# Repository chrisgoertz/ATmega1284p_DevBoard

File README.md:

# ATmega1284p_DevBoard
AVR Developement Board
## Features
### LCD Connector
Precofigured Header for standard Character Display pinouts.
### Buttons
8 on board push buttons. 4 with attached pull-up resistor, 4 with
attached pull-down resistor.
### FTDI Connector
Standard FTDI Connector with attachable DTR enable like Arduino. 
So it is possible to reset and programm the MCU via FTDI connection
if a bootloader is flashed and enabled.
### JTAG Connector
2 AVR JTAG Headers for programming and debugging.
### ISP
Standard 6-pin AVR ISP.
### Serial
6-pin connector with UART0 and UART1 and also VCC and GND.
### I²C
6-Pin Connector with SDA and SCL, VCC, GND and GPIO D7.
### LED-BARs
2 10-Channel LED-Bars, attached to PortA and PortC. 
Both channels can be separate enabled by jumper. Since all
LEDs are decoupled via MOSFETs, they don't affect the GPIOs.

## Pictures

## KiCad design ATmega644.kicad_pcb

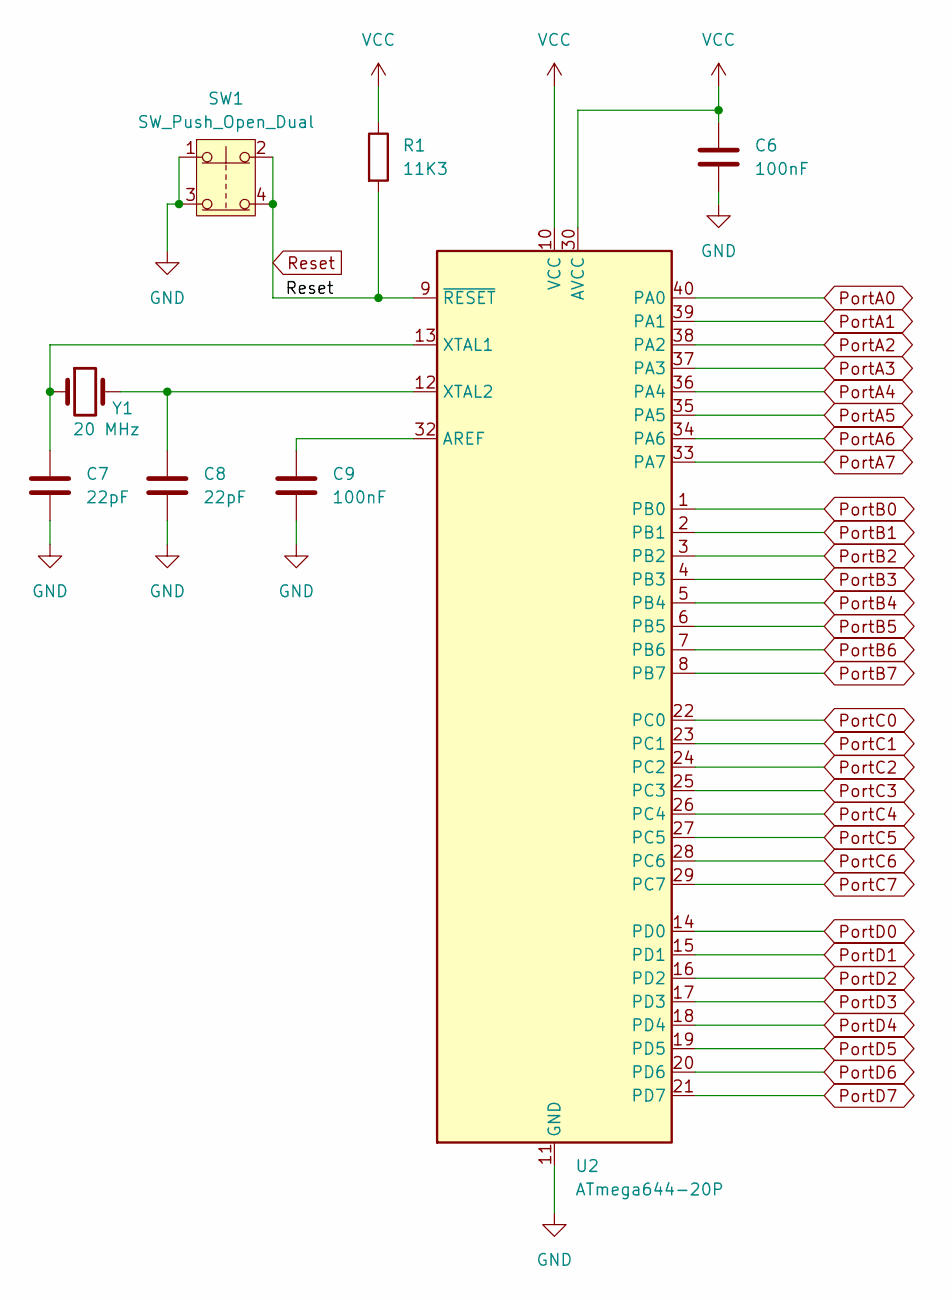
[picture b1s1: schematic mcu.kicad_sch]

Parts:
C6, C9: 100nF; C_0805_2012Metric_Pad1.18x1.45mm_HandSolder
C7, C8: 22pF; C_0805_2012Metric_Pad1.18x1.45mm_HandSolder
R1: 11K3; C_0805_2012Metric_Pad1.18x1.45mm_HandSolder
SW1: SW_Push_Open_Dual; SW_PUSH_6mm
U2: ATmega644-20P; DIP-40_W15.24mm
Y1: 20 MHz; Crystal_HC49-4H_Vertical

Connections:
GND: C6.2, C7.2, C8.2, C9.2, SW1.1, SW1.3, U2.11 (GND), U2.31 (GND); also elsewhere on the board
unnamed: C9.1, U2.32 (AREF)
unnamed: C7.1, U2.13 (XTAL1), Y1.1
unnamed: C8.1, U2.12 (XTAL2), Y1.2
PortA0: U2.40 (PA0); also elsewhere on the board
PortA1: U2.39 (PA1); also elsewhere on the board
PortA2: U2.38 (PA2); also elsewhere on the board
PortA3: U2.37 (PA3); also elsewhere on the board
PortA4: U2.36 (PA4); also elsewhere on the board
PortA5: U2.35 (PA5); also elsewhere on the board
PortA6: U2.34 (PA6); also elsewhere on the board
PortA7: U2.33 (PA7); also elsewhere on the board
PortB0: U2.1 (PB0); also elsewhere on the board
PortB1: U2.2 (PB1); also elsewhere on the board
PortB2: U2.3 (PB2); also elsewhere on the board
PortB3: U2.4 (PB3); also elsewhere on the board
PortB4: U2.5 (PB4); also elsewhere on the board
PortB5: U2.6 (PB5); also elsewhere on the board
PortB6: U2.7 (PB6); also elsewhere on the board
PortB7: U2.8 (PB7); also elsewhere on the board
PortC0: U2.22 (PC0); also elsewhere on the board
PortC1: U2.23 (PC1); also elsewhere on the board
PortC2: U2.24 (PC2); also elsewhere on the board
PortC3: U2.25 (PC3); also elsewhere on the board
PortC4: U2.26 (PC4); also elsewhere on the board
PortC5: U2.27 (PC5); also elsewhere on the board
PortC6: U2.28 (PC6); also elsewhere on the board
PortC7: U2.29 (PC7); also elsewhere on the board
PortD0: U2.14 (PD0); also elsewhere on the board
PortD1: U2.15 (PD1); also elsewhere on the board
PortD2: U2.16 (PD2); also elsewhere on the board
PortD3: U2.17 (PD3); also elsewhere on the board
PortD4: U2.18 (PD4); also elsewhere on the board
PortD5: U2.19 (PD5); also elsewhere on the board
PortD6: U2.20 (PD6); also elsewhere on the board
PortD7: U2.21 (PD7); also elsewhere on the board
Reset: R1.2, SW1.2, SW1.4, U2.9 (~RESET); also elsewhere on the board
VCC: C6.1, R1.1, U2.10 (VCC), U2.30 (AVCC); also elsewhere on the board

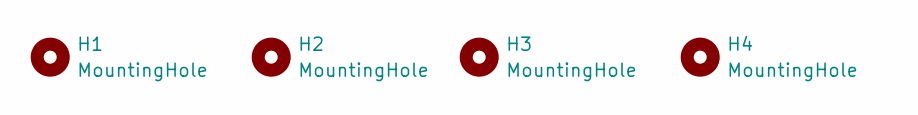
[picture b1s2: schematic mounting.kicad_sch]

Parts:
H1, H2, H3, H4: MountingHole; MountingHole_3.2mm_M3_DIN965

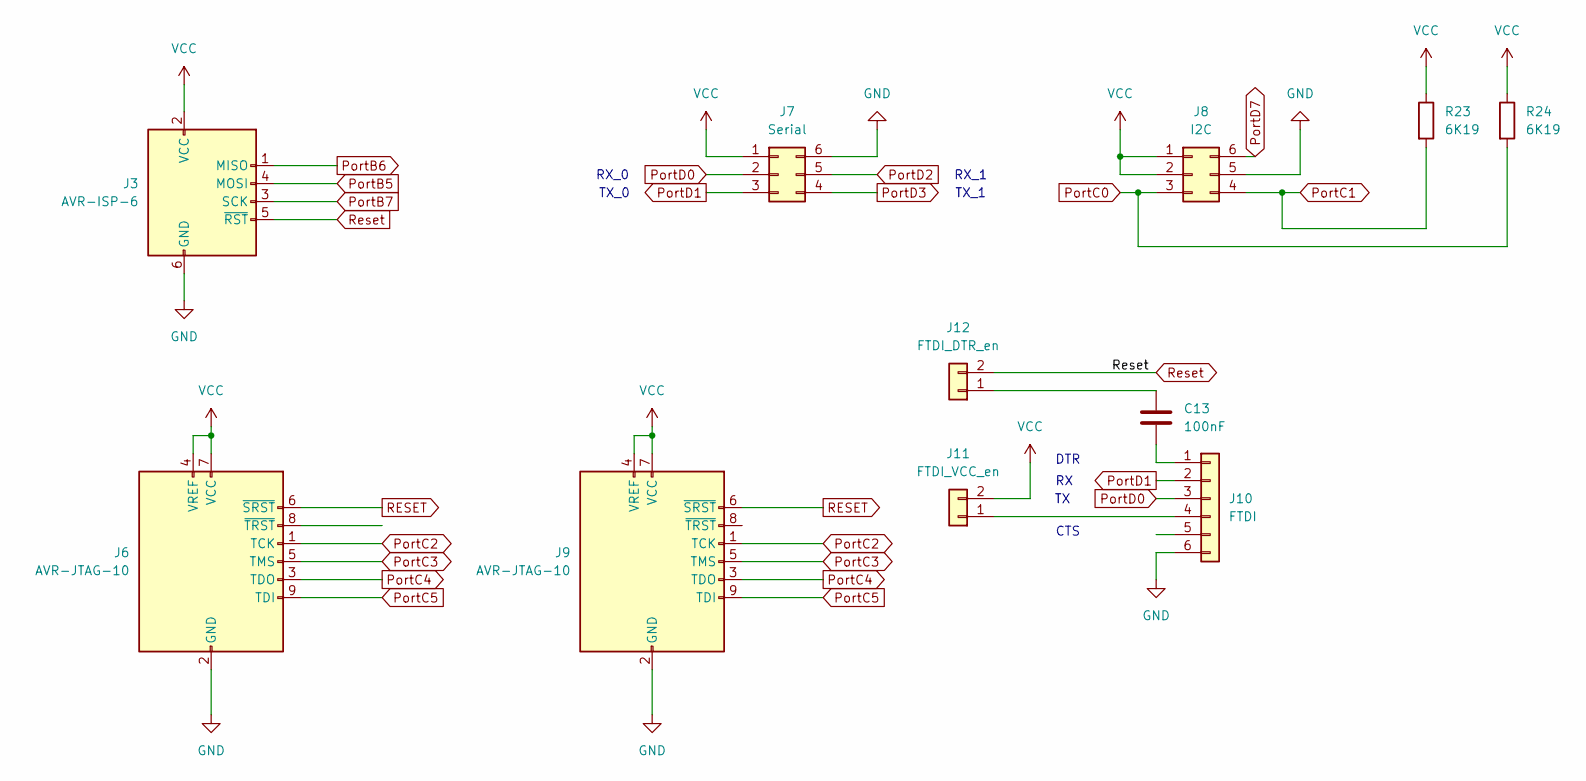
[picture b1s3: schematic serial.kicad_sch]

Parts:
C13: 100nF; LED_0805_2012Metric_Pad1.15x1.40mm_HandSolder
J3: AVR-ISP-6; IDC-Header_2x03_P2.54mm_Vertical
J6: AVR-JTAG-10; PinHeader_2x05_P2.54mm_Vertical
J7: Serial; IDC-Header_2x03_P2.54mm_Vertical
J8: I2C; IDC-Header_2x03_P2.54mm_Vertical
J9: AVR-JTAG-10; PinHeader_2x05_P1.27mm_Vertical_SMD
J10: FTDI; PinHeader_1x06_P2.54mm_Vertical
J11: FTDI_VCC_en; PinHeader_1x02_P2.54mm_Vertical
J12: FTDI_DTR_en; PinHeader_1x02_P2.54mm_Vertical
R23, R24: 6K19; L_1206_3216Metric_Pad1.42x1.75mm_HandSolder

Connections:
GND: J3.6 (GND), J6.2 (GND), J6.10 (GND), J7.6, J8.5, J9.2 (GND), J9.10 (GND), J10.6; also elsewhere on the board
unnamed: C13.2, J10.1
unnamed: J10.4, J11.1
unnamed: C13.1, J12.1
PortB5: J3.4 (MOSI); also elsewhere on the board
PortB6: J3.1 (MISO); also elsewhere on the board
PortB7: J3.3 (SCK); also elsewhere on the board
PortC0: J8.3, R24.2; also elsewhere on the board
PortC1: J8.4, R23.2; also elsewhere on the board
PortC2: J6.1 (TCK), J9.1 (TCK); also elsewhere on the board
PortC3: J6.5 (TMS), J9.5 (TMS); also elsewhere on the board
PortC4: J6.3 (TDO), J9.3 (TDO); also elsewhere on the board
PortC5: J6.9 (TDI), J9.9 (TDI); also elsewhere on the board
PortD0: J7.2, J10.3; also elsewhere on the board
PortD1: J7.3, J10.2; also elsewhere on the board
PortD2: J7.5; also elsewhere on the board
PortD3: J7.4; also elsewhere on the board
PortD7: J8.6; also elsewhere on the board
RESET: J6.6 (~SRST), J9.6 (~SRST)
Reset: J3.5 (~RST), J12.2; also elsewhere on the board
VCC: J3.2 (VCC), J6.4 (VREF), J6.7 (VCC), J7.1, J8.1, J8.2, J9.4 (VREF), J9.7 (VCC), J11.2, R23.1, R24.1; also elsewhere on the board

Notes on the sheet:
TX_0
TX_1
CTS
RX_0
DTR
RX_1

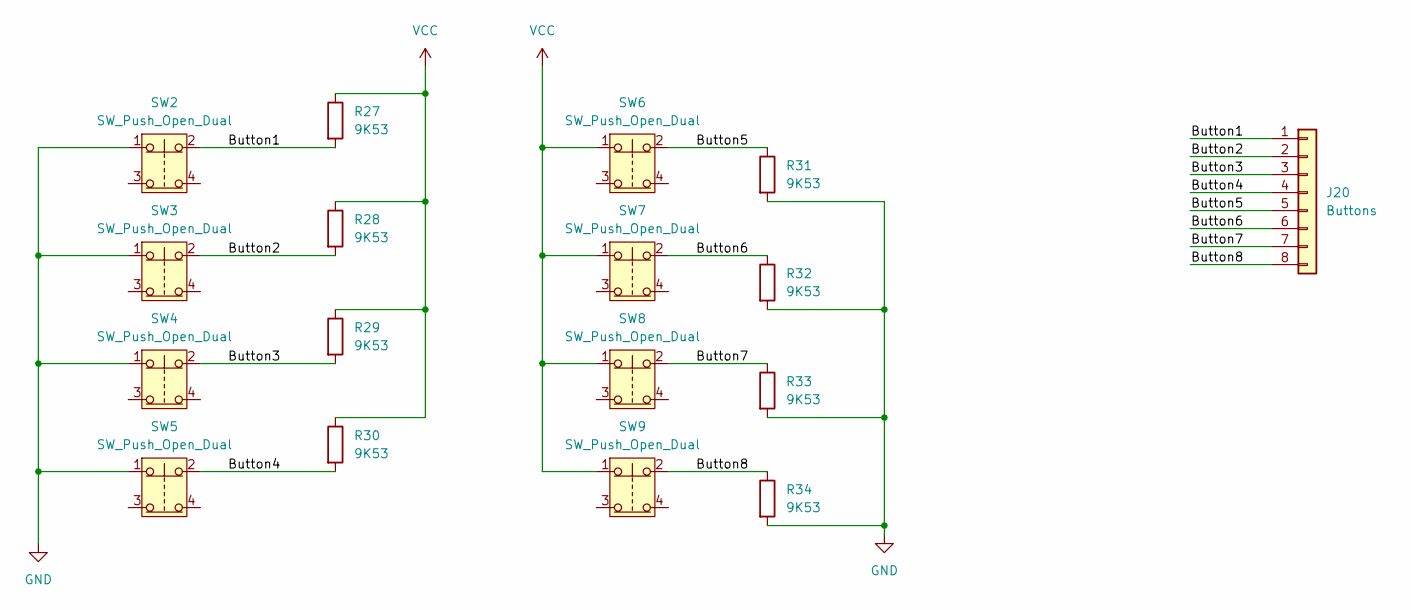
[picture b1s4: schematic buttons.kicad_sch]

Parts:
J20: Buttons; PinHeader_1x08_P2.54mm_Vertical
R27, R28, R29, R30, R31, R32, R33, R34: 9K53; L_1206_3216Metric_Pad1.42x1.75mm_HandSolder
SW2, SW3, SW4, SW5, SW6, SW7, SW8, SW9: SW_Push_Open_Dual; SW_PUSH_6mm

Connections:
/Buttons/Button1: J20.1, R27.2, SW2.2
/Buttons/Button2: J20.2, R28.2, SW3.2
/Buttons/Button3: J20.3, R29.2, SW4.2
/Buttons/Button4: J20.4, R30.2, SW5.2
/Buttons/Button5: J20.5, R31.1, SW6.2
/Buttons/Button6: J20.6, R32.1, SW7.2
/Buttons/Button7: J20.7, R33.1, SW8.2
/Buttons/Button8: J20.8, R34.1, SW9.2
GND: R31.2, R32.2, R33.2, R34.2, SW2.1, SW3.1, SW4.1, SW5.1; also elsewhere on the board
VCC: R27.1, R28.1, R29.1, R30.1, SW6.1, SW7.1, SW8.1, SW9.1; also elsewhere on the board

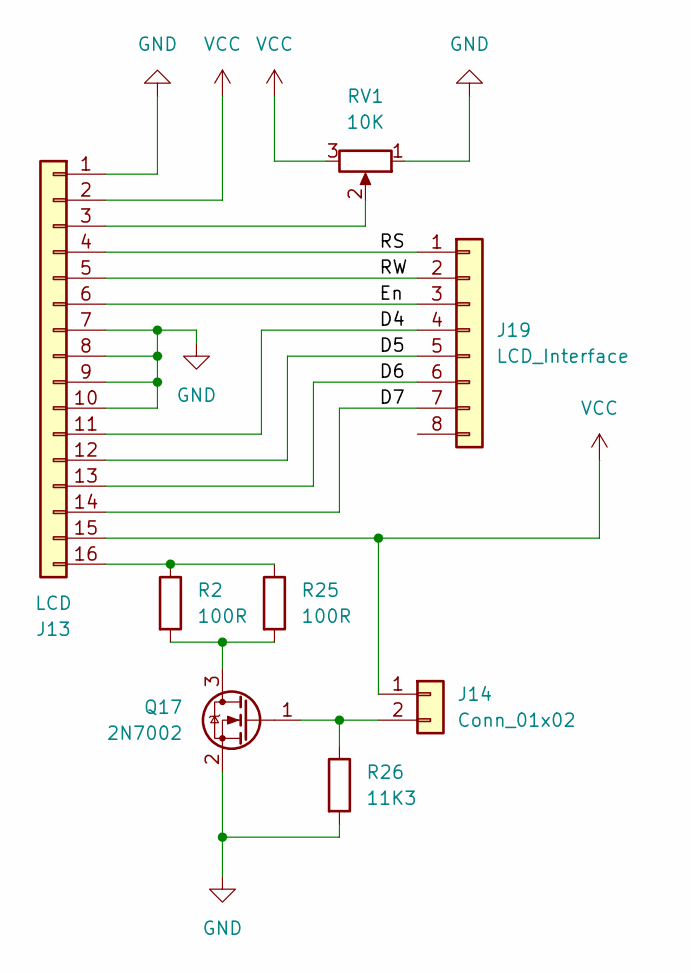
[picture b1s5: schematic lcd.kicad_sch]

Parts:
J13: LCD; PinHeader_1x16_P2.54mm_Vertical
J14: Conn_01x02; PinHeader_1x02_P2.54mm_Vertical
J19: LCD_Interface; PinHeader_1x08_P2.54mm_Vertical
Q17: 2N7002; SOT-23
R2, R25: 100R; LED_0805_2012Metric_Pad1.15x1.40mm_HandSolder
R26: 11K3; LED_0805_2012Metric_Pad1.15x1.40mm_HandSolder
RV1: 10K; Potentiometer_Piher_PT-6-V_Vertical

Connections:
/LCD/D4: J13.11, J19.4
/LCD/D5: J13.12, J19.5
/LCD/D6: J13.13, J19.6
/LCD/D7: J13.14, J19.7
/LCD/En: J13.6, J19.3
/LCD/RS: J13.4, J19.1
/LCD/RW: J13.5, J19.2
GND: J13.1, J13.7, J13.8, J13.9, J13.10, Q17.2 (S), R26.2, RV1.1; also elsewhere on the board
unnamed: J13.3, RV1.2
unnamed: J13.16, R2.1, R25.1
unnamed: J14.2, Q17.1 (G), R26.1
unnamed: Q17.3 (D), R2.2, R25.2
VCC: J13.2, J13.15, J14.1, RV1.3; also elsewhere on the board

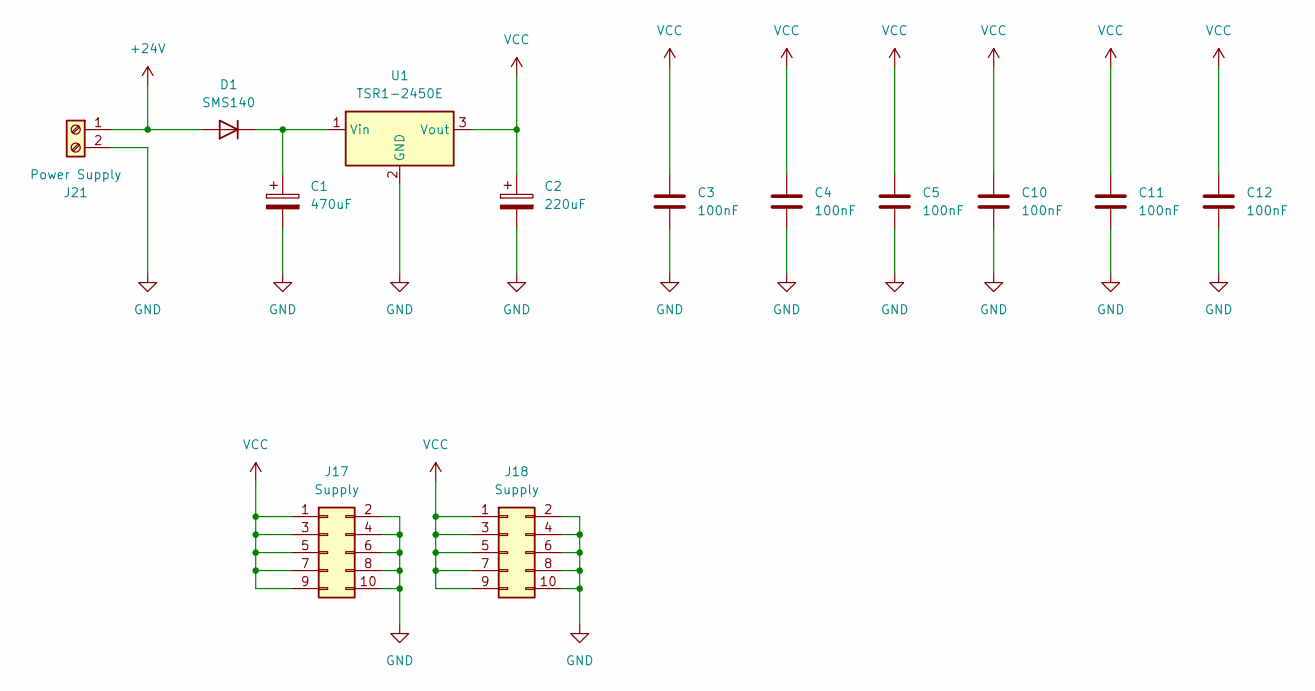
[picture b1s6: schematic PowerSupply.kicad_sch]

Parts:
C1: 470uF; CP_Radial_D10.0mm_P5.00mm
C2: 220uF; CP_Radial_D6.3mm_P2.50mm
C3, C4, C5, C10, C11, C12: 100nF; C_0805_2012Metric_Pad1.18x1.45mm_HandSolder
D1: SMS140; D_SMB_Handsoldering
J17, J18: Supply; PinHeader_2x05_P2.54mm_Vertical
J21: Power Supply; TerminalBlock_bornier-2_P5.08mm
U1: TSR1-2450E; Converter_DCDC_TRACO_TSR1-xxxxE_THT

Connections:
+24V: D1.2 (A), J21.1
GND: C1.2, C2.2, C3.2, C4.2, C5.2, C10.2, C11.2, C12.2, J17.2, J17.4, J17.6, J17.8, J17.10, J18.2, J18.4, J18.6, J18.8, J18.10, J21.2, U1.2 (GND); also elsewhere on the board
unnamed: C1.1, D1.1 (K), U1.1 (Vin)
VCC: C2.1, C3.1, C4.1, C5.1, C10.1, C11.1, C12.1, J17.1, J17.3, J17.5, J17.7, J17.9, J18.1, J18.3, J18.5, J18.7, J18.9, U1.3 (Vout); also elsewhere on the board

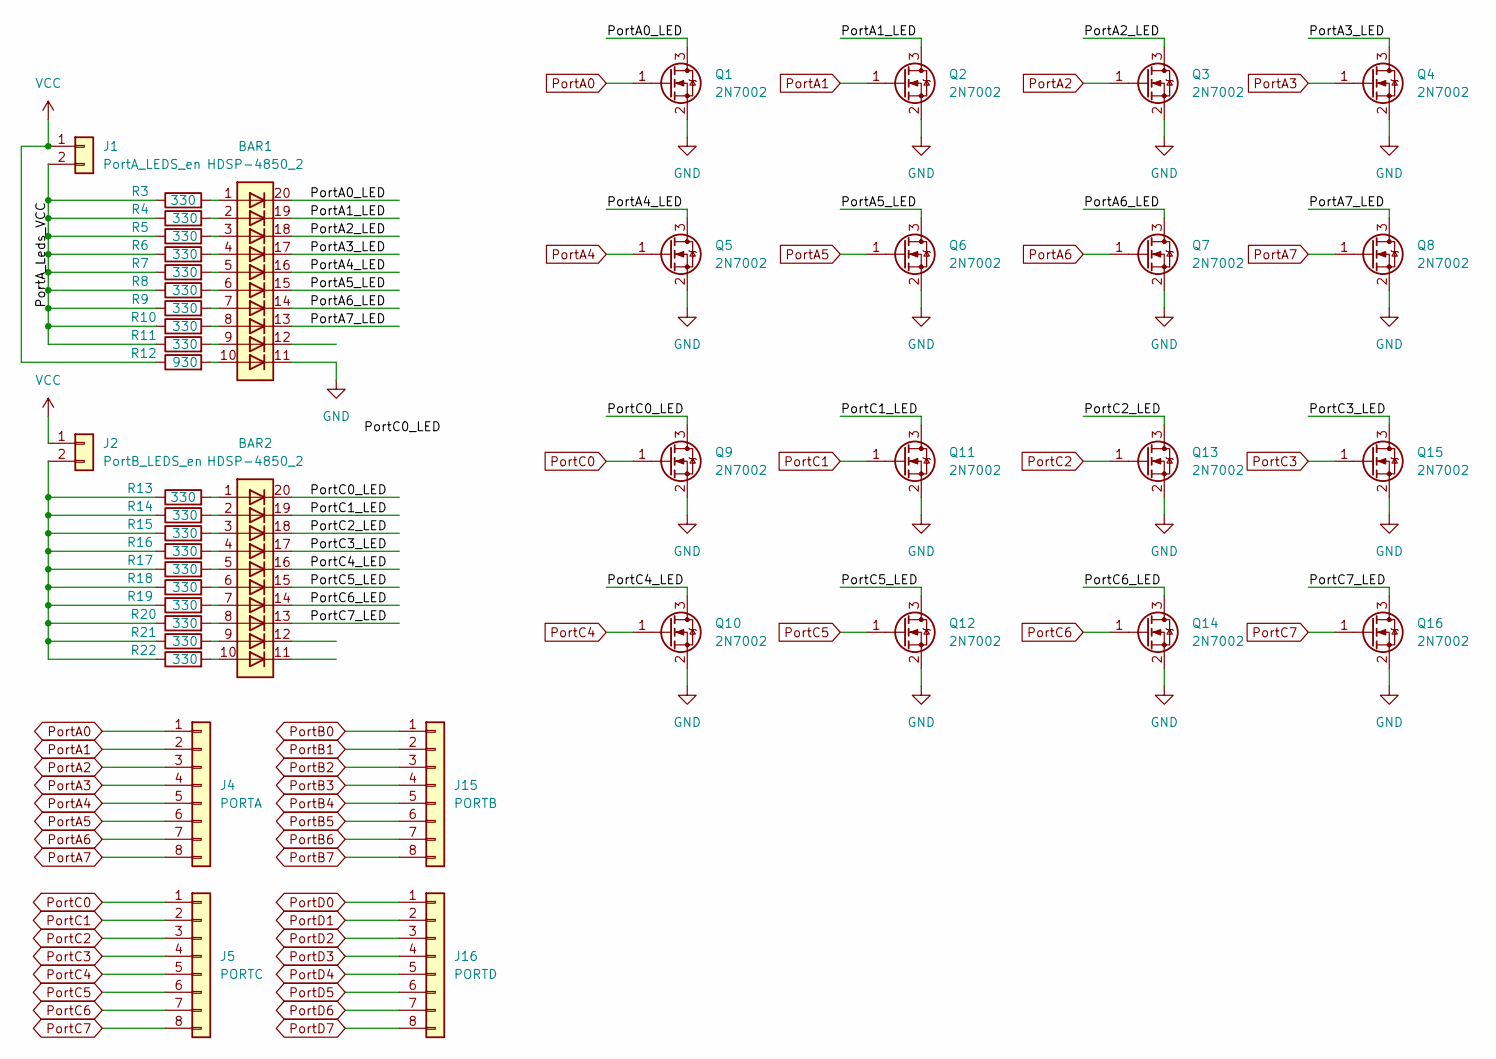
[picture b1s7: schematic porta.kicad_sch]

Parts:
BAR1, BAR2: HDSP-4850_2; HDSP-4850
J1: PortA_LEDS_en; PinHeader_1x02_P2.54mm_Vertical
J2: PortB_LEDS_en; PinHeader_1x02_P2.54mm_Vertical
J4: PORTA; PinHeader_1x08_P2.54mm_Vertical
J5: PORTC; PinHeader_1x08_P2.54mm_Vertical
J15: PORTB; PinHeader_1x08_P2.54mm_Vertical
J16: PORTD; PinHeader_1x08_P2.54mm_Vertical
Q1, Q2, Q3, Q4, Q5, Q6, Q7, Q8, Q9, Q10, Q11, Q12, Q13, Q14, Q15, Q16: 2N7002; SOT-23
R3, R4, R5, R6, R7, R8, R9, R10, R11, R13, R14, R15, R16, R17, R18, R19, R20, R21, R22: 330; C_0805_2012Metric_Pad1.18x1.45mm_HandSolder
R12: 930; C_0805_2012Metric_Pad1.18x1.45mm_HandSolder

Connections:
/PORTS/PortA0_LED: BAR1.20 (K), Q1.3 (D)
/PORTS/PortA1_LED: BAR1.19 (K), Q2.3 (D)
/PORTS/PortA2_LED: BAR1.18 (K), Q3.3 (D)
/PORTS/PortA3_LED: BAR1.17 (K), Q4.3 (D)
/PORTS/PortA4_LED: BAR1.16 (K), Q5.3 (D)
/PORTS/PortA5_LED: BAR1.15 (K), Q6.3 (D)
/PORTS/PortA6_LED: BAR1.14 (K), Q7.3 (D)
/PORTS/PortA7_LED: BAR1.13 (K), Q8.3 (D)
/PORTS/PortA_Leds_VCC: J1.2, R3.1, R4.1, R5.1, R6.1, R7.1, R8.1, R9.1, R10.1, R11.1
/PORTS/PortC0_LED: BAR2.20 (K), Q9.3 (D)
/PORTS/PortC1_LED: BAR2.19 (K), Q11.3 (D)
/PORTS/PortC2_LED: BAR2.18 (K), Q13.3 (D)
/PORTS/PortC3_LED: BAR2.17 (K), Q15.3 (D)
/PORTS/PortC4_LED: BAR2.16 (K), Q10.3 (D)
/PORTS/PortC5_LED: BAR2.15 (K), Q12.3 (D)
/PORTS/PortC6_LED: BAR2.14 (K), Q14.3 (D)
/PORTS/PortC7_LED: BAR2.13 (K), Q16.3 (D)
GND: BAR1.11 (K), Q1.2 (S), Q2.2 (S), Q3.2 (S), Q4.2 (S), Q5.2 (S), Q6.2 (S), Q7.2 (S), Q8.2 (S), Q9.2 (S), Q10.2 (S), Q11.2 (S), Q12.2 (S), Q13.2 (S), Q14.2 (S), Q15.2 (S), Q16.2 (S); also elsewhere on the board
unnamed: BAR1.1 (A), R3.2
unnamed: BAR1.2 (A), R4.2
unnamed: BAR1.3 (A), R5.2
unnamed: BAR1.4 (A), R6.2
unnamed: BAR1.5 (A), R7.2
unnamed: BAR1.6 (A), R8.2
unnamed: BAR1.7 (A), R9.2
unnamed: BAR1.8 (A), R10.2
unnamed: BAR1.9 (A), R11.2
unnamed: BAR1.10 (A), R12.2
unnamed: BAR2.1 (A), R13.2
unnamed: BAR2.2 (A), R14.2
unnamed: BAR2.3 (A), R15.2
unnamed: BAR2.4 (A), R16.2
unnamed: BAR2.5 (A), R17.2
unnamed: BAR2.6 (A), R18.2
unnamed: BAR2.7 (A), R19.2
unnamed: BAR2.8 (A), R20.2
unnamed: BAR2.9 (A), R21.2
unnamed: BAR2.10 (A), R22.2
unnamed: J2.2, R13.1, R14.1, R15.1, R16.1, R17.1, R18.1, R19.1, R20.1, R21.1, R22.1
PortA0: J4.1, Q1.1 (G); also elsewhere on the board
PortA1: J4.2, Q2.1 (G); also elsewhere on the board
PortA2: J4.3, Q3.1 (G); also elsewhere on the board
PortA3: J4.4, Q4.1 (G); also elsewhere on the board
PortA4: J4.5, Q5.1 (G); also elsewhere on the board
PortA5: J4.6, Q6.1 (G); also elsewhere on the board
PortA6: J4.7, Q7.1 (G); also elsewhere on the board
PortA7: J4.8, Q8.1 (G); also elsewhere on the board
PortB0: J15.1; also elsewhere on the board
PortB1: J15.2; also elsewhere on the board
PortB2: J15.3; also elsewhere on the board
PortB3: J15.4; also elsewhere on the board
PortB4: J15.5; also elsewhere on the board
PortB5: J15.6; also elsewhere on the board
PortB6: J15.7; also elsewhere on the board
PortB7: J15.8; also elsewhere on the board
PortC0: J5.1, Q9.1 (G); also elsewhere on the board
PortC1: J5.2, Q11.1 (G); also elsewhere on the board
PortC2: J5.3, Q13.1 (G); also elsewhere on the board
PortC3: J5.4, Q15.1 (G); also elsewhere on the board
PortC4: J5.5, Q10.1 (G); also elsewhere on the board
PortC5: J5.6, Q12.1 (G); also elsewhere on the board
PortC6: J5.7, Q14.1 (G); also elsewhere on the board
PortC7: J5.8, Q16.1 (G); also elsewhere on the board
PortD0: J16.1; also elsewhere on the board
PortD1: J16.2; also elsewhere on the board
PortD2: J16.3; also elsewhere on the board
PortD3: J16.4; also elsewhere on the board
PortD4: J16.5; also elsewhere on the board
PortD5: J16.6; also elsewhere on the board
PortD6: J16.7; also elsewhere on the board
PortD7: J16.8; also elsewhere on the board
VCC: J1.1, J2.1, R12.1; also elsewhere on the board

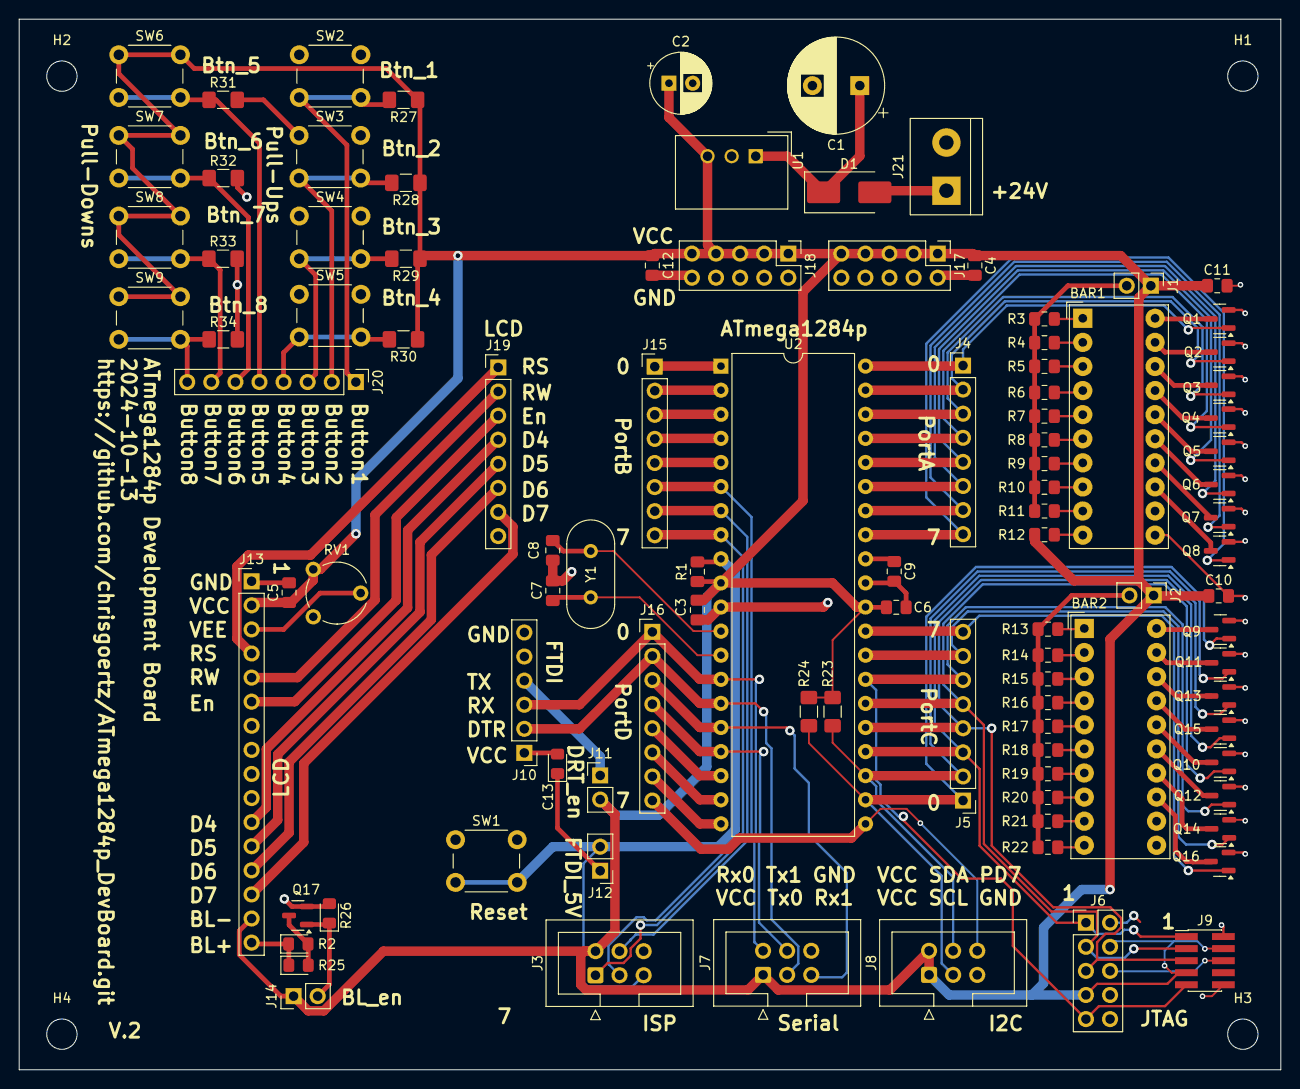
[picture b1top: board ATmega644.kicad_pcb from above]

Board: 2 copper layers, 133.0 x 110.8 mm, 105 parts (0 on the bottom side), 101 nets.

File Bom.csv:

"ID";"Bezeichner";"Footprint";"Stückzahl";"Bezeichnung";"Anbieter und Referenz";
1;"SW2,SW5,SW1,SW6,SW3,SW7,SW8,SW9,SW4";"SW_PUSH_6mm";9;"SW_Push_Open_Dual";;;
2;"J12";"PinHeader_1x02_P2.54mm_Vertical";1;"FTDI_DTR_en";;;
3;"Q7,Q8,Q2,Q1,Q4,Q11,Q14,Q16,Q6,Q13,Q12,Q9,Q5,Q10,Q17,Q3,Q15";"SOT-23";17;"2N7002";;;
4;"R24,R23";"L_1206_3216Metric_Pad1.42x1.75mm_HandSolder";2;"6K19";;;
5;"R29,R32,R33,R34,R28,R31,R30,R27";"L_1206_3216Metric_Pad1.42x1.75mm_HandSolder";8;"9K53";;;
6;"R11,R20,R21,R15,R17,R14,R10,R8,R18,R4,R7,R16,R9,R6,R19,R22,R3,R13,R5";"C_0805_2012Metric_Pad1.18x1.45mm_HandSolder";19;"330";;;
7;"J17,J18";"PinHeader_2x05_P2.54mm_Vertical";2;"Supply";;;
8;"R1";"C_0805_2012Metric_Pad1.18x1.45mm_HandSolder";1;"11K3";;;
9;"J20";"PinHeader_1x08_P2.54mm_Vertical";1;"Buttons";;;
10;"R26";"LED_0805_2012Metric_Pad1.15x1.40mm_HandSolder";1;"11K3";;;
11;"BAR1,BAR2";"HDSP-4850";2;"HDSP-4850_2";;;
12;"J21";"TerminalBlock_bornier-2_P5.08mm";1;"Power Supply";;;
13;"J9";"PinHeader_2x05_P1.27mm_Vertical_SMD";1;"AVR-JTAG-10";;;
14;"C11,C4,C9,C10,C3,C6,C12,C5";"C_0805_2012Metric_Pad1.18x1.45mm_HandSolder";8;"100nF";;;
15;"C8,C7";"C_0805_2012Metric_Pad1.18x1.45mm_HandSolder";2;"22pF";;;
16;"J5";"PinHeader_1x08_P2.54mm_Vertical";1;"PORTC";;;
17;"R25,R2";"LED_0805_2012Metric_Pad1.15x1.40mm_HandSolder";2;"100R";;;
18;"J6";"PinHeader_2x05_P2.54mm_Vertical";1;"AVR-JTAG-10";;;
19;"C1";"CP_Radial_D10.0mm_P5.00mm";1;"470uF";;;
20;"RV1";"Potentiometer_Piher_PT-6-V_Vertical";1;"10K";;;
21;"J10";"PinHeader_1x06_P2.54mm_Vertical";1;"FTDI";;;
22;"J13";"PinHeader_1x16_P2.54mm_Vertical";1;"LCD";;;
23;"C13";"LED_0805_2012Metric_Pad1.15x1.40mm_HandSolder";1;"100nF";;;
24;"J4";"PinHeader_1x08_P2.54mm_Vertical";1;"PORTA";;;
25;"C2";"CP_Radial_D6.3mm_P2.50mm";1;"220uF";;;
26;"J19";"PinHeader_1x08_P2.54mm_Vertical";1;"LCD_Interface";;;
27;"J2";"PinHeader_1x02_P2.54mm_Vertical";1;"PortB_LEDS_en";;;
28;"U2";"DIP-40_W15.24mm";1;"ATmega644-20P";;;
29;"J3";"IDC-Header_2x03_P2.54mm_Vertical";1;"AVR-ISP-6";;;
30;"J7";"IDC-Header_2x03_P2.54mm_Vertical";1;"Serial";;;
31;"Y1";"Crystal_HC49-4H_Vertical";1;"20 MHz";;;
32;"J8";"IDC-Header_2x03_P2.54mm_Vertical";1;"I2C";;;
33;"J14";"PinHeader_1x02_P2.54mm_Vertical";1;"Conn_01x02";;;
34;"U1";"Converter_DCDC_TRACO_TSR1-xxxxE_THT";1;"TSR1-2450E";;;
35;"J1";"PinHeader_1x02_P2.54mm_Vertical";1;"PortA_LEDS_en";;;
36;"D1";"D_SMB_Handsoldering";1;"SMS140";;;
37;"J15";"PinHeader_1x08_P2.54mm_Vertical";1;"PORTB";;;
38;"R12";"C_0805_2012Metric_Pad1.18x1.45mm_HandSolder";1;"930";;;
39;"J11";"PinHeader_1x02_P2.54mm_Vertical";1;"FTDI_VCC_en";;;
40;"J16";"PinHeader_1x08_P2.54mm_Vertical";1;"PORTD";;;

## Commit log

2024-11-01 initial release
2024-11-01 added bill of material
2024-11-01 added gerber files
2024-11-01 added pix
2024-11-01 added readme
